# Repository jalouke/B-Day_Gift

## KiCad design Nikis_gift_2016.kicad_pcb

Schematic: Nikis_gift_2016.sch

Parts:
3V1: Battery; CR2032H-2
C1, C2, C6: 10 microF; C_0805_HandSoldering
C3: C; C_0805_HandSoldering
C4, C5: 22 pF; C_0805_HandSoldering
CON1: BARREL_JACK
D1, D2: LED; LED-5MM
IC1: ATMEGA328P-A; TQFP-32_7x7mm_Pitch0.8mm
LED1: CONN_01X03; Socket_Strip_Straight_1x03
O1: 16 Mhz; Crystal_HC49-U_Vertical
O2: 32.768kHz; Crystal_Round_Horizontal_3mm_BigPad
P1: CONN_01X06; Pin_Header_Straight_1x06
R1, R2: 220; R_0805_HandSoldering
R3, R6, R7, R8, R9: 10k; R_0805_HandSoldering
R4, R5: 4.7k; R_0805_HandSoldering
SW1: SW_PUSH; SW_PUSH_SMALL
SW2, SW3, SW4, SW5: SW_PUSH; Socket_Strip_Straight_1x02
U1: LM7805CT; TO-220_Neutral123_PadsOnly
U2: DS1338; SOIC-8_3.9x4.9mm_Pitch1.27mm
USB1: CONN_01X06; Socket_Strip_Straight_1x06

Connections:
+5V: C2.2, C6.1, IC1.4 (VCC), IC1.6 (VCC), LED1.3, P1.6, R1.1, R3.2, SW2.2, SW3.2, SW4.2, SW5.2, U1.3, U2.8 (VCC), USB1.4
GND: 3V1.2, C1.1, C2.1, C4.1, C5.1, C6.2, CON1.1, CON1.3, D2.1, IC1.3 (GND), IC1.5 (GND), IC1.21 (GND), LED1.1, P1.5, R2.1, R4.1, R5.1, R6.1, R7.1, R8.1, R9.1, SW1.2, U1.2, U2.4 (GND), USB1.5, USB1.6
unnamed: 3V1.1, U2.3 (Vbat)
unnamed: C1.2, CON1.2, U1.1
unnamed: C3.1, IC1.29 ((PCINT14/~RESET~)PC6), P1.4, R3.1, SW1.1
unnamed: C3.2, USB1.1
unnamed: C4.2, IC1.7 ((PCINT6/XTAL1/TOSC1)PB6), O1.1
unnamed: C5.2, IC1.8 ((PCINT7/XTAL2/TOSC2)PB7), O1.2
unnamed: D1.1, R2.2
unnamed: D1.2, IC1.17 ((PCINT5/SCK)PB5), P1.3
unnamed: D2.2, R1.2
unnamed: IC1.1 ((PCINT19/OC2B/INT1)PD3), R6.2, SW2.1
unnamed: IC1.2 ((PCINT20/XCK/T0)PD4), R7.2, SW3.1
unnamed: IC1.9 ((PCINT21/OC0B/T1)PD5), R8.2, SW4.1
unnamed: IC1.10 ((PCINT22/OC0A/AIN0)PD6), R9.2, SW5.1
unnamed: IC1.12 ((PCINT0/CLKO/ICP1)PB0), LED1.2
unnamed: IC1.15 ((PCINT3/OC2A/MOSI)PB3), P1.1
unnamed: IC1.16 ((PCINT4/MISO)PB4), P1.2
unnamed: IC1.27 ((PCINT12/SDA/ADC4)PC4), R4.2, U2.5 (SDA)
unnamed: IC1.28 ((PCINT13/SCL/ADC5)PC5), R5.2, U2.6 (SCL)
unnamed: IC1.30 ((PCINT16/RXD)PD0), USB1.3
unnamed: IC1.31 ((PCINT17/TXD)PD1), USB1.2
unnamed: O2.1, U2.1 (X1)
unnamed: O2.2, U2.2 (X2)

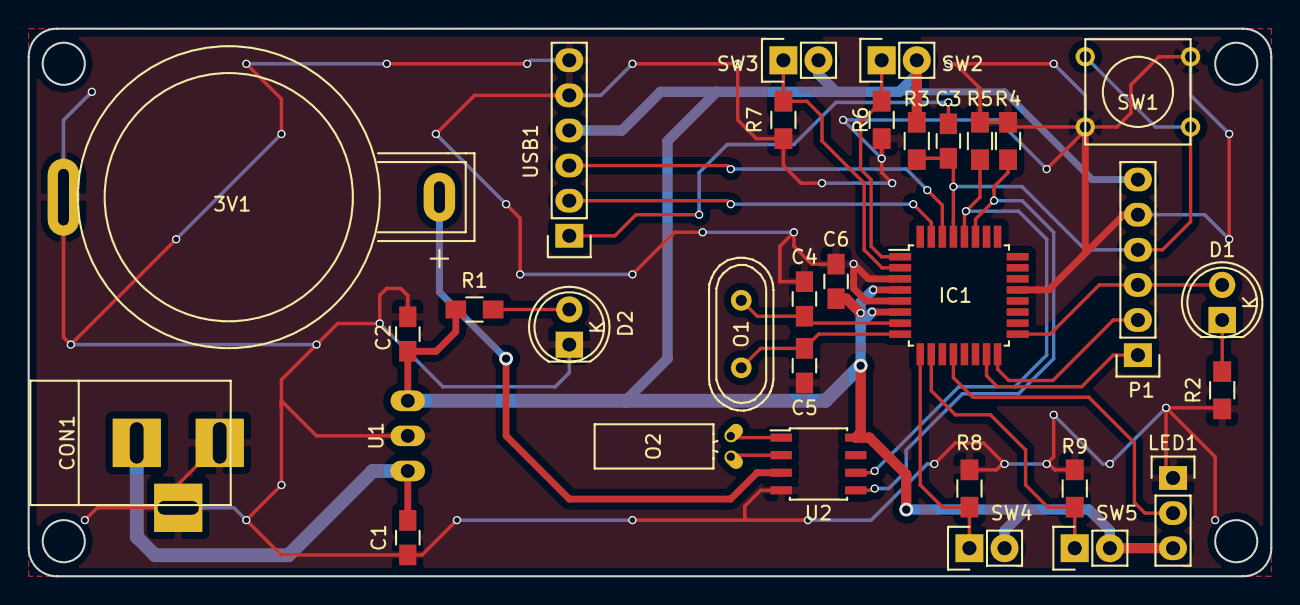
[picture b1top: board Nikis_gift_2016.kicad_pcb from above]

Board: 2 copper layers, 89.9 x 39.6 mm, 32 parts (0 on the bottom side), 24 nets.

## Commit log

2016-05-30 designing the clock
2016-06-03 updating layout and schematic
2016-06-03 all fixed
2016-06-04 gerber
2016-06-04 Please enter the commit message for your changes. Lines starting
2016-12-21 adding code and laser cutter plans
